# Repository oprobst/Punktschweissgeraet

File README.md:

# Punktschweissgeraet

Schaltpläne, Layouts und Software

See http://www.tief-dunkel-kalt.org/index.php/blog/42-diy-punktschweissgeraet for details (sorry, German only).

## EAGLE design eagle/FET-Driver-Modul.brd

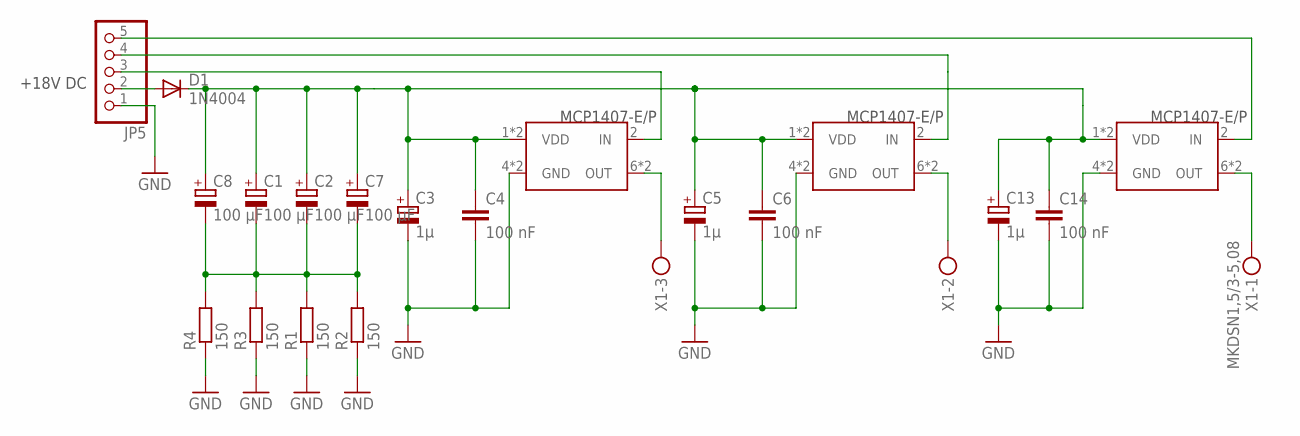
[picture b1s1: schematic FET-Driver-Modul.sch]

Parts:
C1, C2, C7, C8: 100 µF; E2,5-7
C3, C5, C13: 1µ; E5-8,5
C4, C6, C14: 100 nF; C0603
D1: 1N4004; DO41-10
JP5: PINHD-1X5; 1X05
R1, R2, R3, R4: 150; 0411/15
U$3, U$4, U$5: MCP1407MCP1407-DIL08; DIL-08
X1: MKDSN1,5/3-5,08

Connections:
GND: C3.-, C4.2, C5.-, C6.2, C13.-, C14.2, JP5.1, R1.1, R2.1, R3.1, R4.1, U$3.4 (GND), U$3.5 (GND), U$4.4 (GND), U$4.5 (GND), U$5.4 (GND), U$5.5 (GND)
unnamed: JP5.4, U$4.2 (IN)
unnamed: C1.+, C2.+, C3.+, C4.1, C5.+, C6.1, C7.+, C8.+, C13.+, C14.1, D1.C, U$3.1 (VDD), U$3.8 (VDD), U$4.1 (VDD), U$4.8 (VDD), U$5.1 (VDD), U$5.8 (VDD)
unnamed: JP5.5, U$5.2 (IN)
unnamed: C1.-, C2.-, C7.-, C8.-, R1.2, R2.2, R3.2, R4.2
unnamed: JP5.3, U$3.2 (IN)
unnamed: D1.A, JP5.2
unnamed: U$4.6 (OUT), U$4.7 (OUT), X1.2
unnamed: U$3.6 (OUT), U$3.7 (OUT), X1.3
unnamed: U$5.6 (OUT), U$5.7 (OUT), X1.1

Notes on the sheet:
+18V DC
MCP1407-E/P

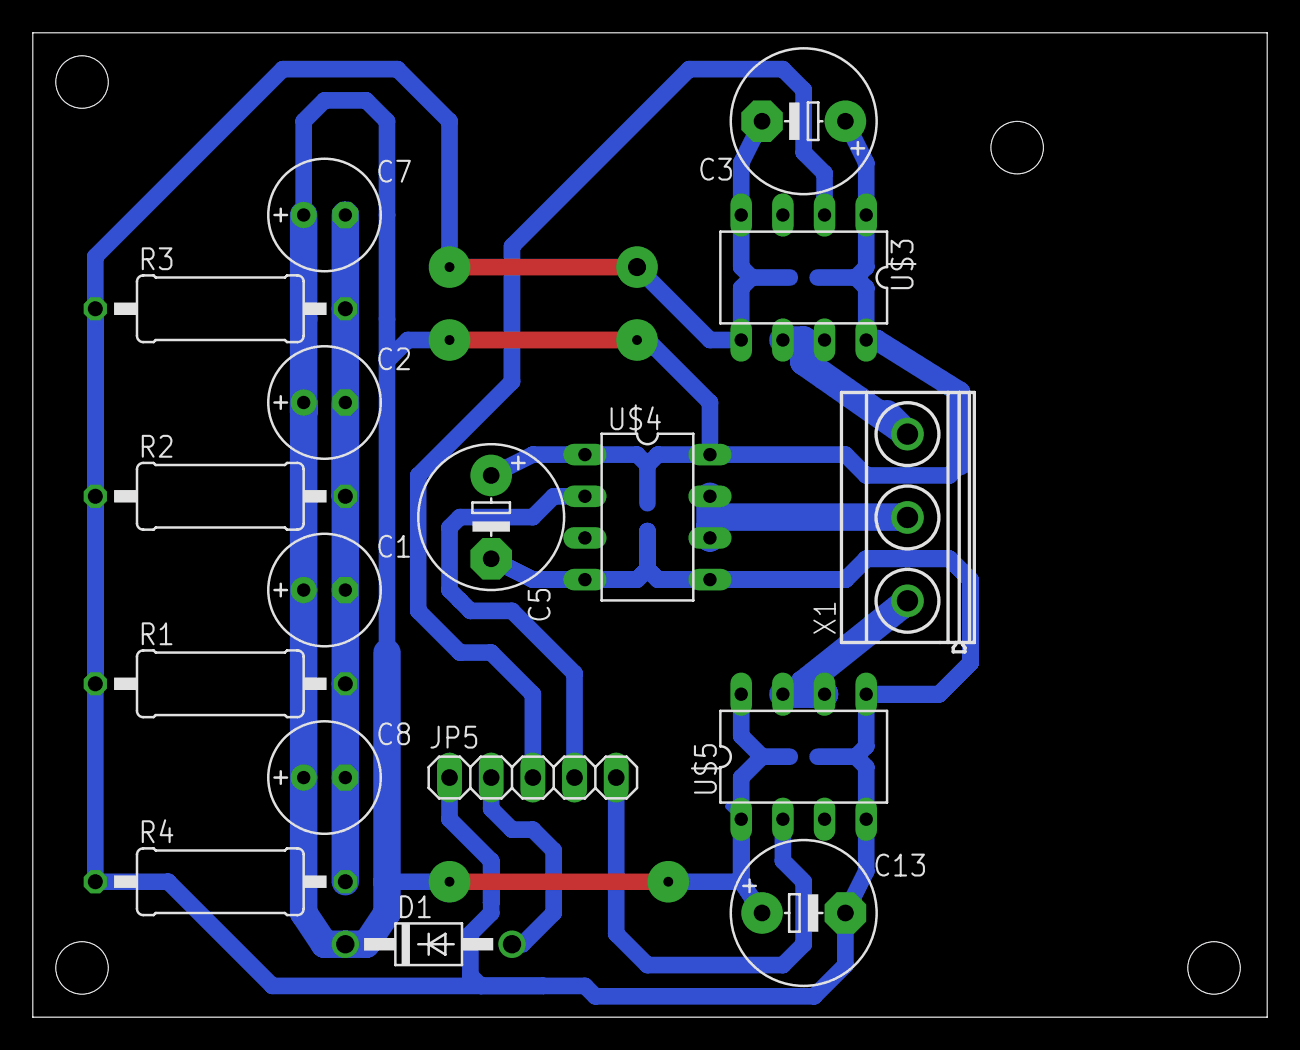
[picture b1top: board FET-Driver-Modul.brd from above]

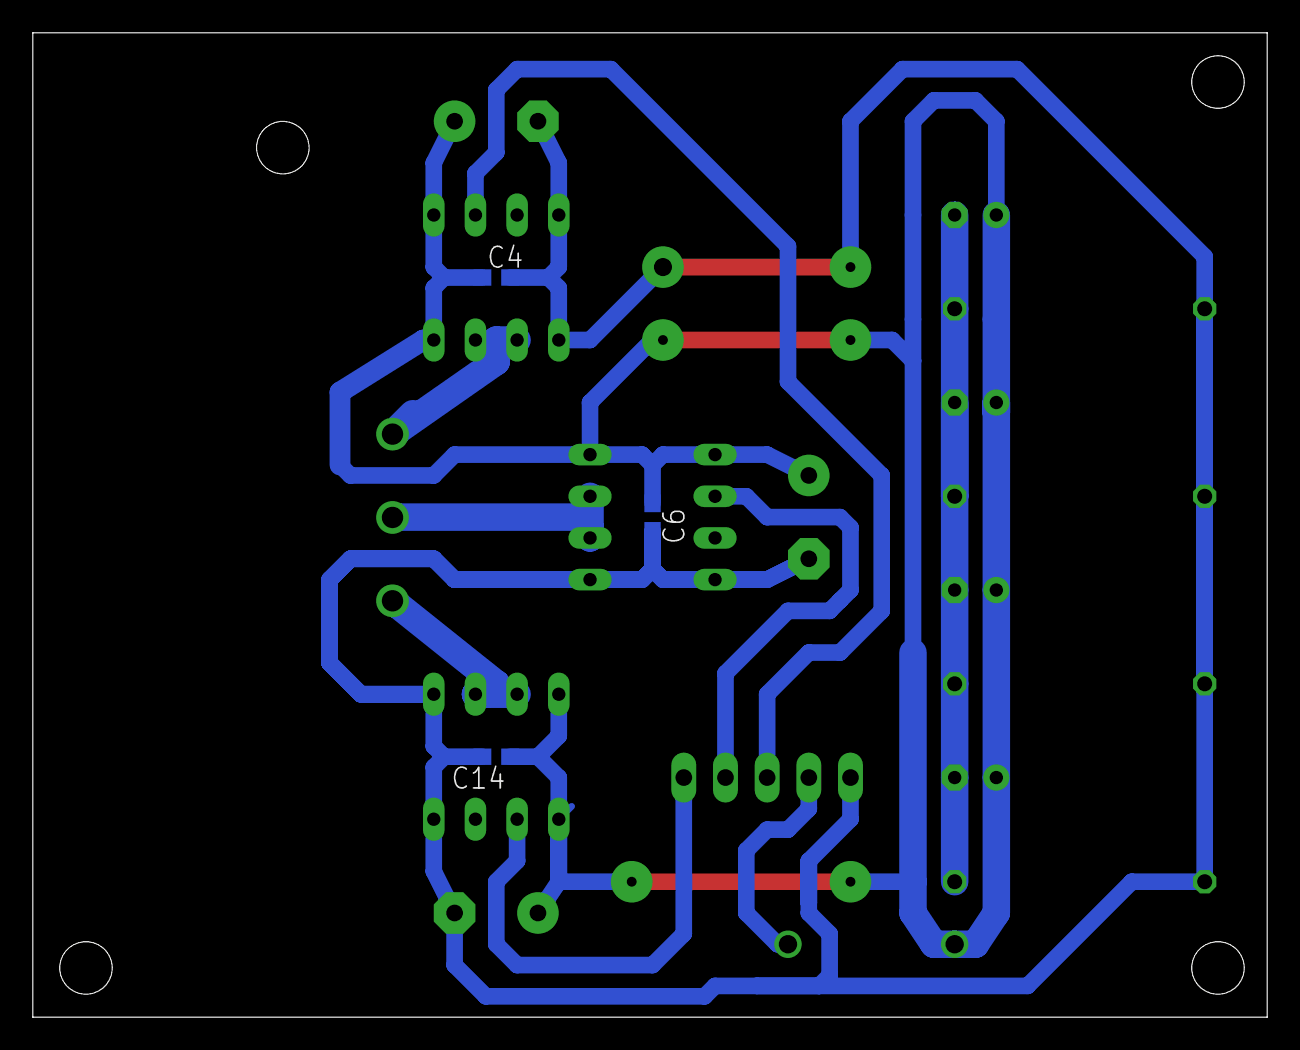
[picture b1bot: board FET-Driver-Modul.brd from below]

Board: 2 copper layers, 75.2 x 60.0 mm, 20 parts (3 on the bottom side), 10 nets.

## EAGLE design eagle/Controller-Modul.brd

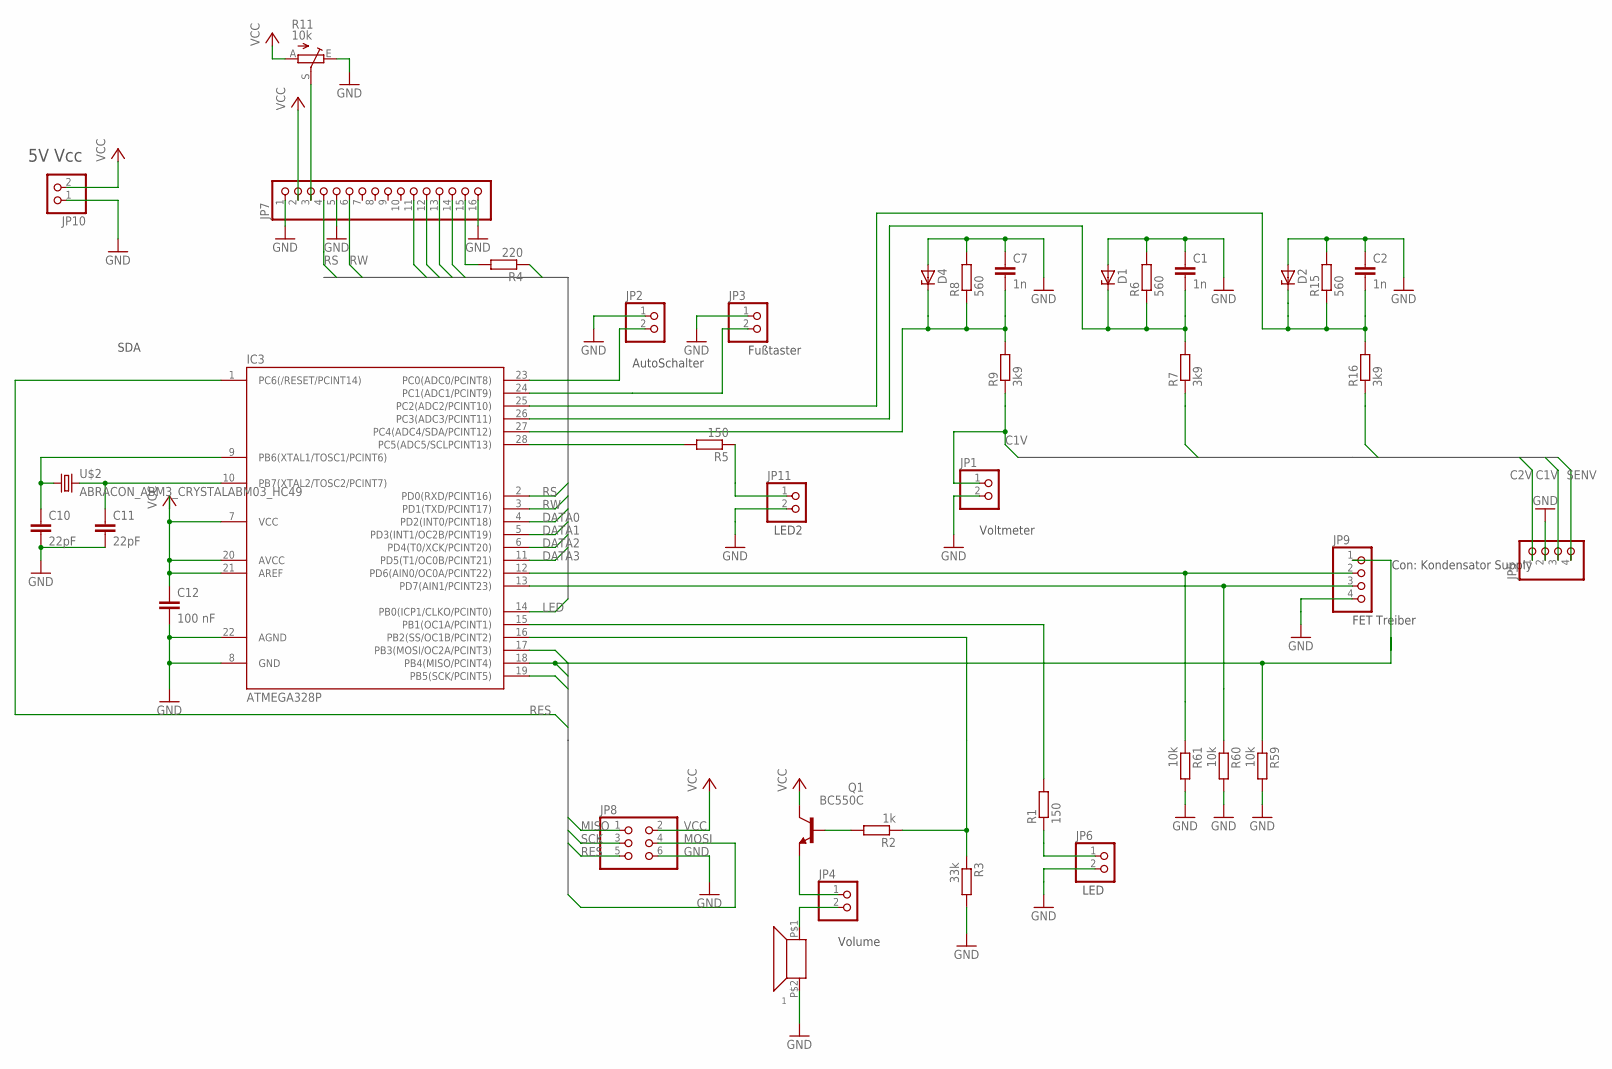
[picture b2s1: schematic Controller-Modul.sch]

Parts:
1: SUMMER4; PIEZO-INDIKATOR-KPMG
C1, C2, C7: 1n; C0603K
C10, C11: 22pF; C0603K
C12: 100 nF; C0603
D1, D2, D4: ZENER-DIODESOT23; SOT23
IC3: ATMEGA328P; DIL28-3
JP1, JP2, JP3, JP4, JP6, JP10, JP11: PINHD-1X2; 1X02
JP5, JP9: PINHD-1X4; 1X04
JP7: PINHD-1X16; 1X16
JP8: PINHD-2X3; 2X03
Q1: BC550C; TO92-EBC
R1, R5: 150; R1206
R2: 1k; R1206
R3: 33k; R1206
R4: 220; R1206
R6, R8, R15: 560; R1206
R7, R9, R16: 3k9; R1206
R11: 10k; PT-10
R59, R60, R61: 10k; R1206
U$2: ABRACON_ABM3_CRYSTALABM03_HC49; ABM03_HC49

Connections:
C1V: JP1.1, JP5.3, R9.1
C2V: JP5.1, R7.1
DATA0: IC3.4 (PD2(INT0/PCINT18)), JP7.11
DATA1: IC3.5 (PD3(INT1/OC2B/PCINT19)), JP7.12
DATA2: IC3.6 (PD4(T0/XCK/PCINT20)), JP7.13
DATA3: IC3.11 (PD5(T1/OC0B/PCINT21)), JP7.14
FET2: IC3.13 (PD7(AIN1/PCINT23)), JP9.3, R60.1
FET3: IC3.12 (PD6(AIN0/OC0A/PCINT22)), JP9.2, R61.1
GND: 1.P$2 (+), C1.1, C2.1, C7.1, C10.2, C11.2, C12.2, D1.1 (A), D2.1 (A), D4.1 (A), IC3.8 (GND), IC3.22 (AGND), JP1.2, JP2.1, JP3.1, JP5.2, JP6.2, JP7.1, JP7.5, JP7.16, JP8.6, JP9.4, JP10.1, JP11.2, R3.2, R6.2, R8.2, R11.E, R15.2, R59.2, R60.2, R61.2
LED: IC3.14 (PB0(ICP1/CLKO/PCINT0)), R4.1
MISO: IC3.18 (PB4(MISO/PCINT4)), JP8.1, JP9.1, R59.1
MOSI: IC3.17 (PB3(MOSI/OC2A/PCINT3)), JP8.4
unnamed: JP11.1, R5.1
unnamed: IC3.28 (PC5(ADC5/SCLPCINT13)), R5.2
unnamed: Q1.B, R2.2
unnamed: C7.2, D4.3 (C), IC3.27 (PC4(ADC4/SDA/PCINT12)), R8.1, R9.2
unnamed: JP6.1, R1.1
unnamed: C1.2, D1.3 (C), IC3.26 (PC3(ADC3/PCINT11)), R6.1, R7.2
unnamed: IC3.16 (PB2(SS/OC1B/PCINT2)), R2.1, R3.1
unnamed: IC3.23 (PC0(ADC0/PCINT8)), JP2.2
unnamed: JP4.1, Q1.E
unnamed: IC3.24 (PC1(ADC1/PCINT9)), JP3.2
unnamed: 1.P$1 (-), JP4.2
unnamed: C2.2, D2.3 (C), IC3.25 (PC2(ADC2/PCINT10)), R15.1, R16.2
unnamed: IC3.15 (PB1(OC1A/PCINT1)), R1.2
unnamed: C11.1, IC3.10 (PB7(XTAL2/TOSC2/PCINT7)), U$2.2
unnamed: C10.1, IC3.9 (PB6(XTAL1/TOSC1/PCINT6)), U$2.1
unnamed: JP7.3, R11.S
unnamed: JP7.15, R4.2
RES: IC3.1 (PC6(/RESET/PCINT14)), JP8.5
RS: IC3.2 (PD0(RXD/PCINT16)), JP7.4
RW: IC3.3 (PD1(TXD/PCINT17)), JP7.6
SCK: IC3.19 (PB5(SCK/PCINT5)), JP8.3
SENV: JP5.4, R16.1
VCC: C12.1, IC3.7 (VCC), IC3.20 (AVCC), IC3.21 (AREF), JP7.2, JP8.2, JP10.2, Q1.C, R11.A

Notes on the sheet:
SDA
5V Vcc
LED
Volume
Con: Kondensator Supply
Voltmeter
Fußtaster
AutoSchalter
FET Treiber
LED2

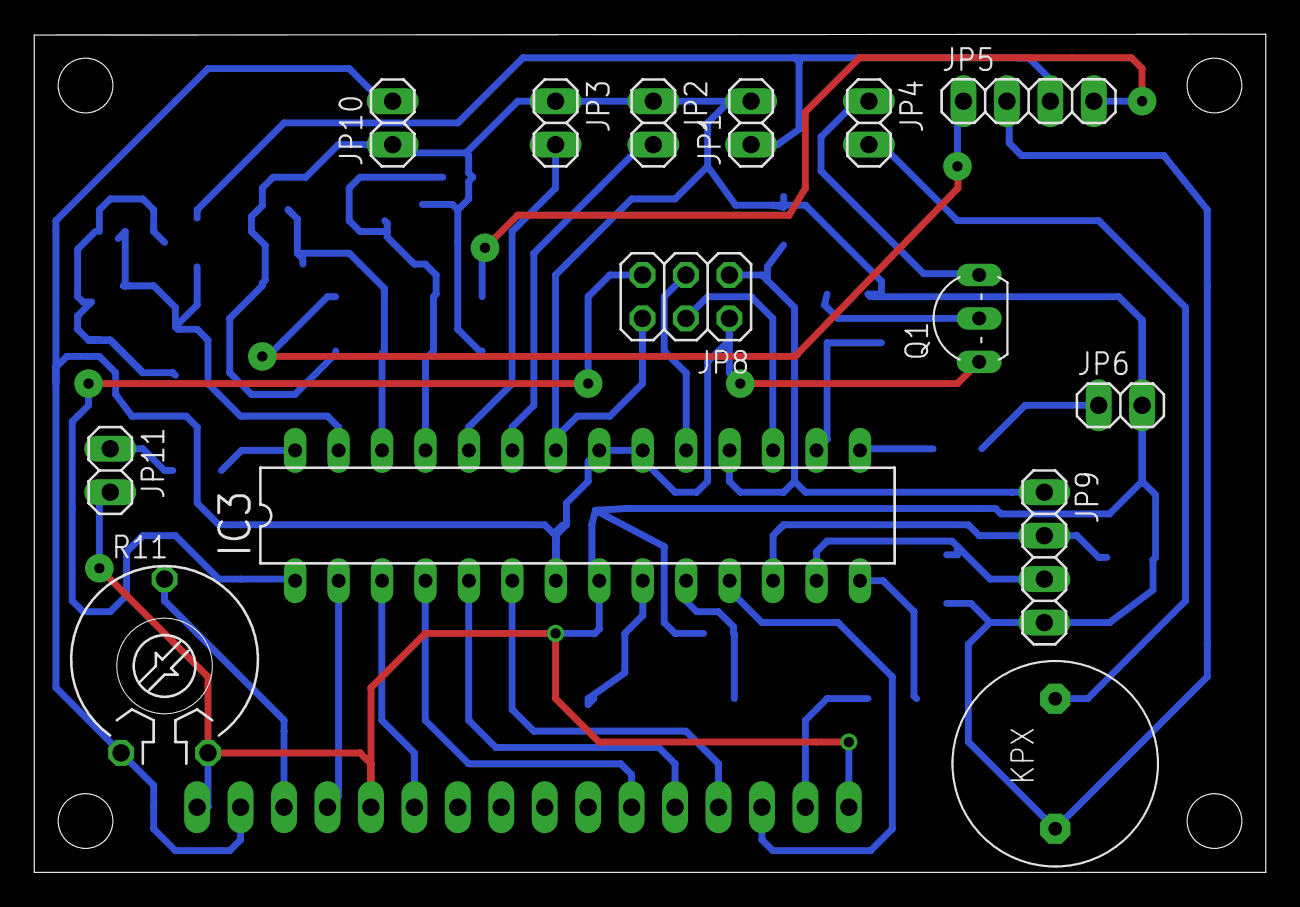
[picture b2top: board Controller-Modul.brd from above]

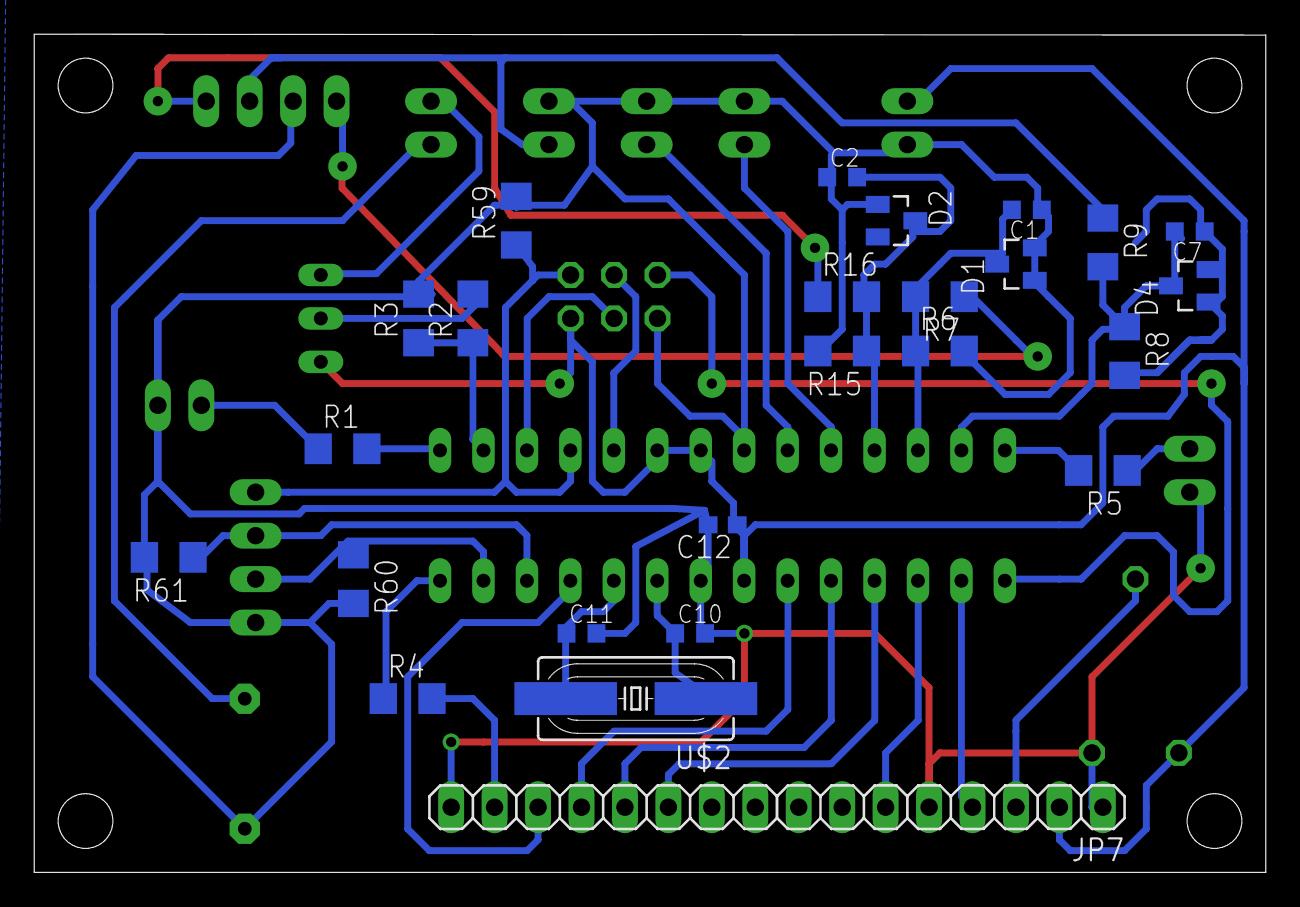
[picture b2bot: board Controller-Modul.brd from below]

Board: 2 copper layers, 72.0 x 49.0 mm, 39 parts (25 on the bottom side), 35 nets.

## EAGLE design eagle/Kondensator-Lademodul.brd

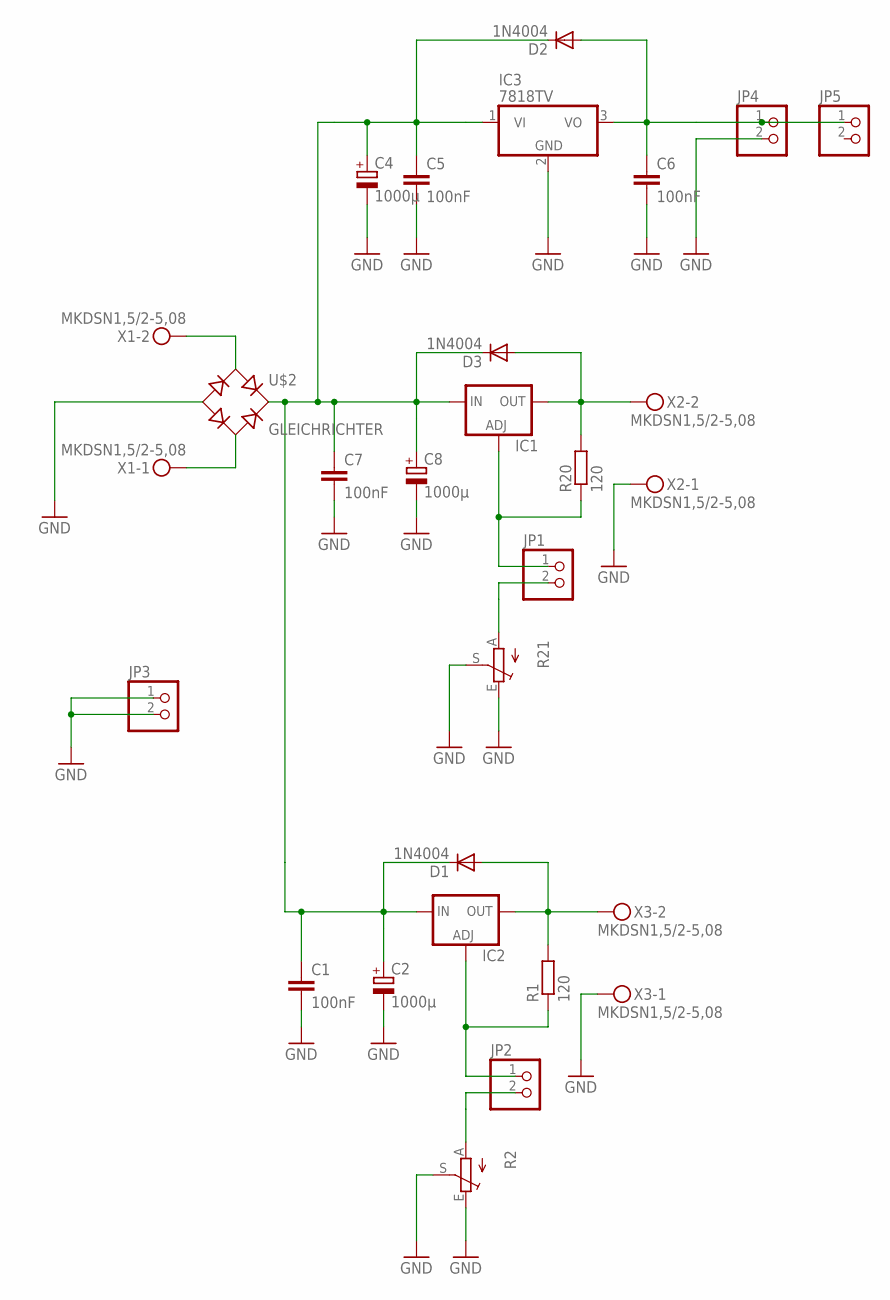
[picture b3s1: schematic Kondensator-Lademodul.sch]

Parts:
C1, C5, C6, C7: 100nF; C0805
C2, C4, C8: 1000µ; E5-13
D1, D2, D3: 1N4004; DO41-10
IC1, IC2: LM317TS; 317TS
IC3: 7818TV; TO220V
JP1, JP2, JP3, JP4, JP5: PINHD-1X2; 1X02
R1, R20: 120; R1206
R2, R21: TRIM_EU-PT10; PT-10
U$2: GLEICHRICHTER; KBPC1
X1, X2, X3: MKDSN1,5/2-5,08

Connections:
GND: C1.2, C2.-, C4.-, C5.2, C6.2, C7.2, C8.-, IC3.2 (GND), JP3.1, JP3.2, JP4.2, JP5.2, R2.E, R2.S, R21.E, R21.S, U$2.-, X2.1, X3.1
unnamed: C6.1, D2.A, IC3.3 (VO), JP4.1, JP5.1
unnamed: D1.A, IC2.2 (OUT), R1.2, X3.2
unnamed: IC2.1 (ADJ), JP2.1, R1.1
unnamed: JP2.2, R2.A
unnamed: C1.1, C2.+, C4.+, C5.1, C7.1, C8.+, D1.C, D2.C, D3.C, IC1.3 (IN), IC2.3 (IN), IC3.1 (VI), U$2.+
unnamed: U$2.AC1, X1.2
unnamed: U$2.AC2, X1.1
unnamed: D3.A, IC1.2 (OUT), R20.2, X2.2
unnamed: JP1.2, R21.A
unnamed: IC1.1 (ADJ), JP1.1, R20.1

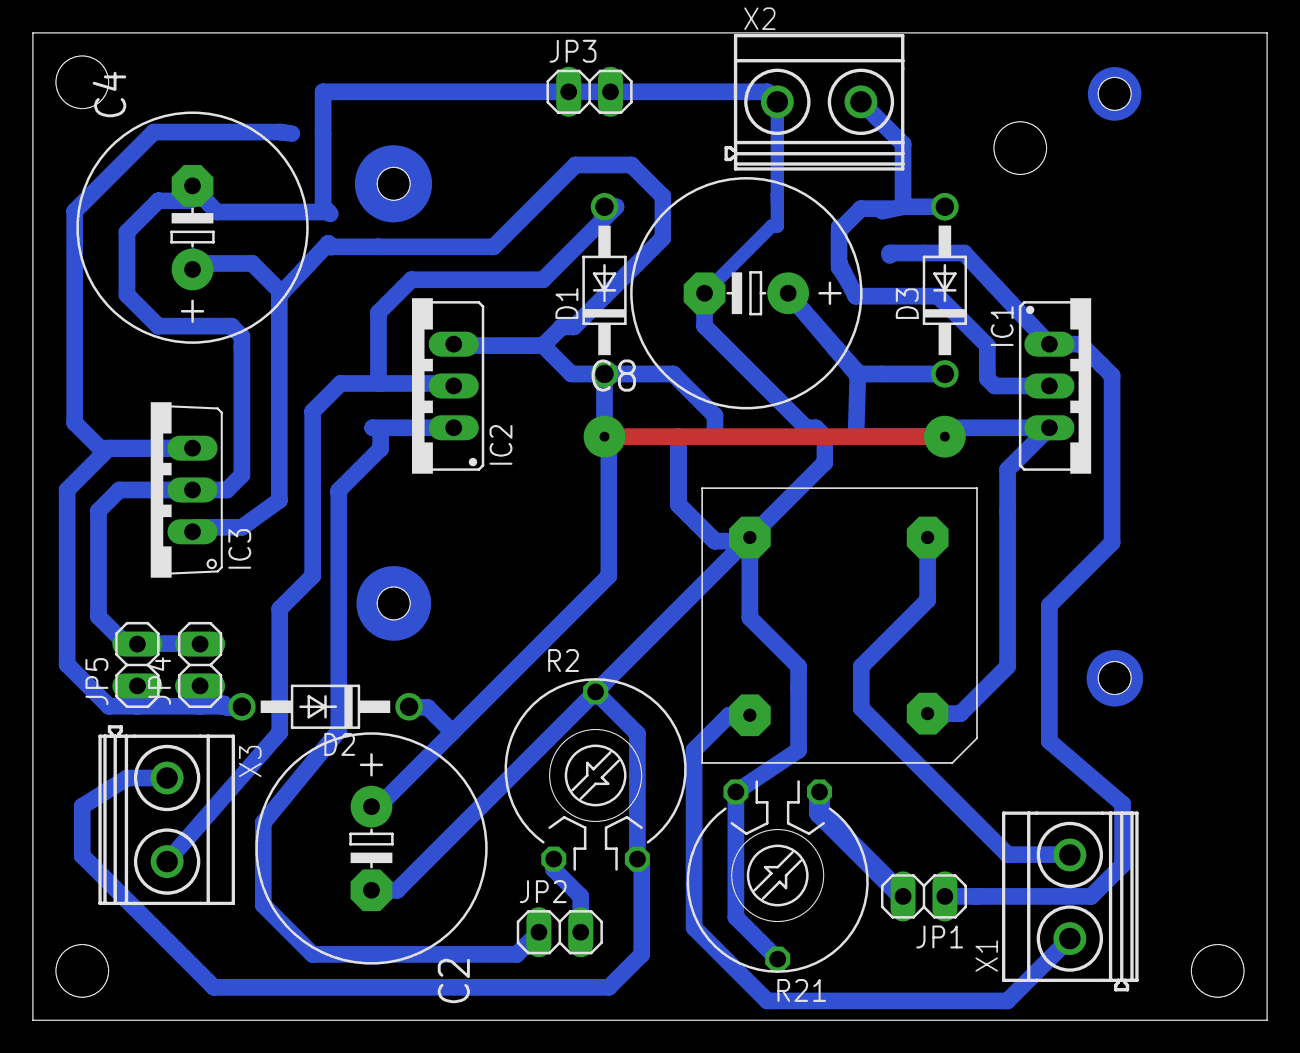
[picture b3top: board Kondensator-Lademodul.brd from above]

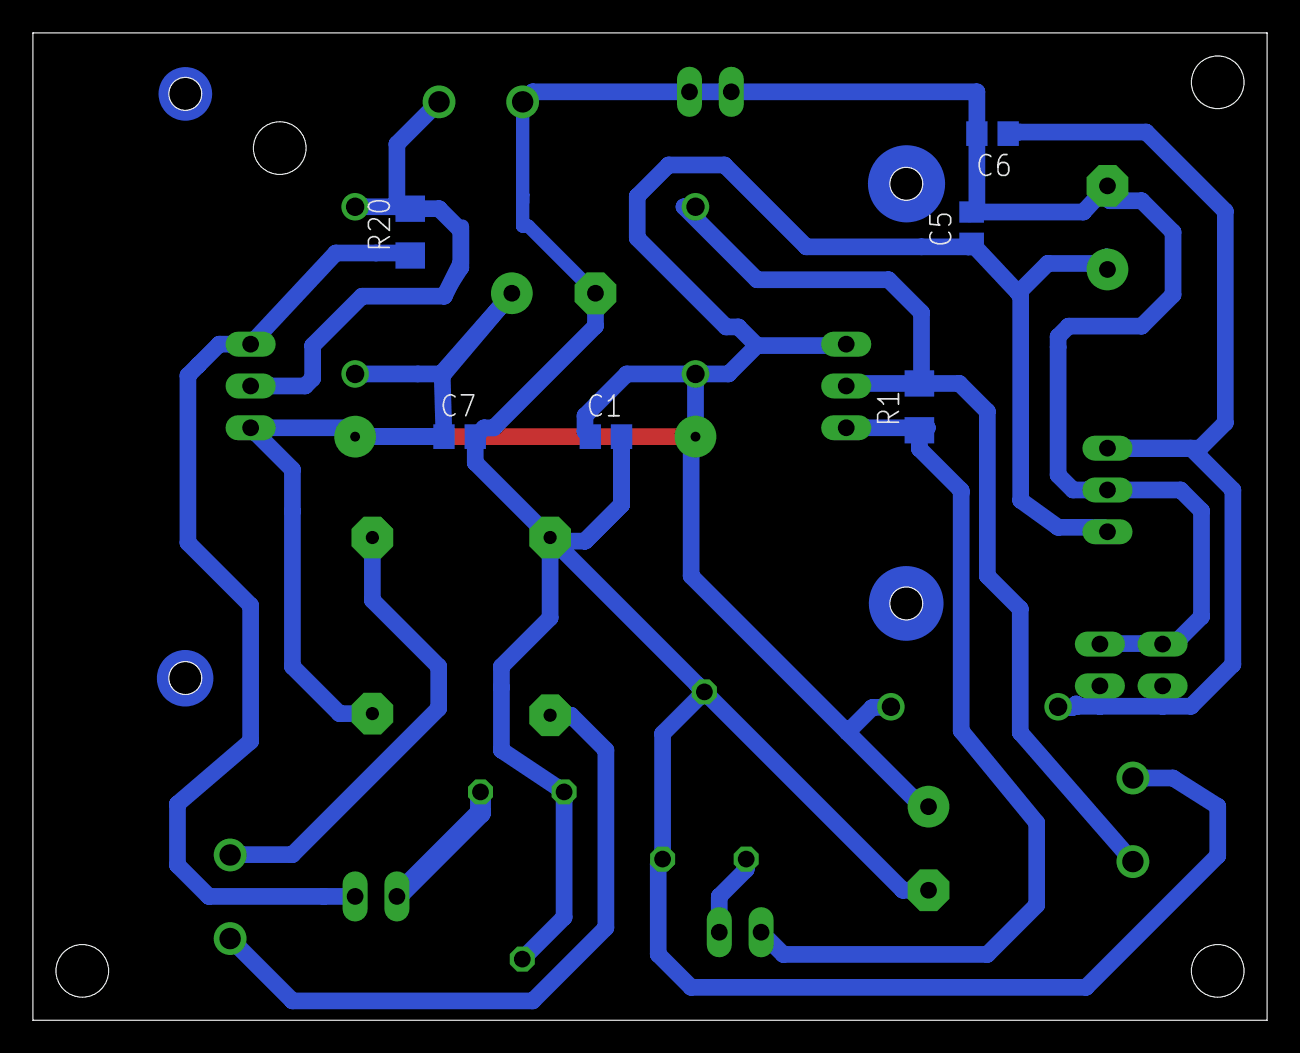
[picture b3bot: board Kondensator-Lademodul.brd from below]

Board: 2 copper layers, 75.0 x 60.0 mm, 26 parts (6 on the bottom side), 11 nets.

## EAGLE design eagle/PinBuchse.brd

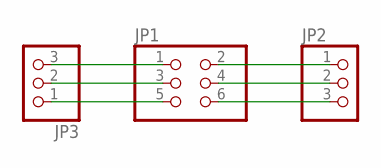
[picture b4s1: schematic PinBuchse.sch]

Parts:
JP1: PINHD-2X3; 2X03
JP2, JP3: PINHD-1X3; 1X03

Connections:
unnamed: JP1.1, JP3.3
unnamed: JP1.3, JP3.2
unnamed: JP1.5, JP3.1
unnamed: JP1.2, JP2.1
unnamed: JP1.4, JP2.2
unnamed: JP1.6, JP2.3

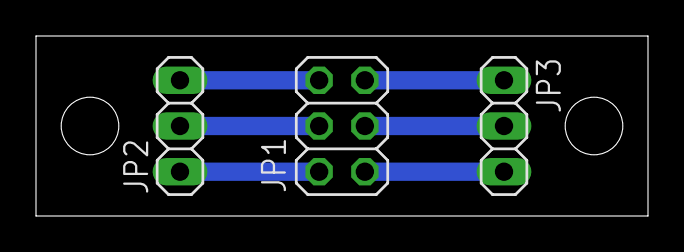
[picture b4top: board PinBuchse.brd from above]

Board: 2 copper layers, 34.0 x 10.0 mm, 3 parts (0 on the bottom side), 6 nets.

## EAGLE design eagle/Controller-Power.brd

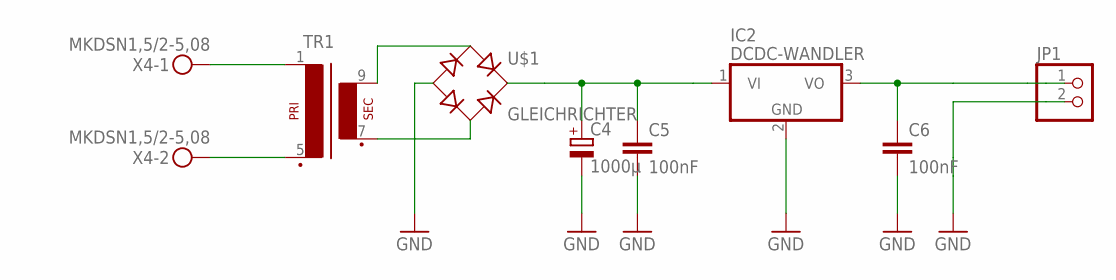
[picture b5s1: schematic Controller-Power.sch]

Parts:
C4: 1000µ; E3,5-8
C5, C6: 100nF; C0805
IC2: DCDC-WANDLER; TRACOPOWER-DCDCWANDER-TSR1
JP1: PINHD-1X2; 1X02
TR1: EI38-1
U$1: GLEICHRICHTER; KBPC1
X4: MKDSN1,5/2-5,08

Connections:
GND: C4.-, C5.2, C6.2, IC2.2 (GND), JP1.2, U$1.-
unnamed: C4.+, C5.1, IC2.1 (VI), U$1.+
unnamed: TR1.1, X4.1
unnamed: TR1.5 (P2), X4.2
unnamed: TR1.7 (S3), U$1.AC2
unnamed: TR1.9 (S4), U$1.AC1
unnamed: C6.1, IC2.3 (VO), JP1.1

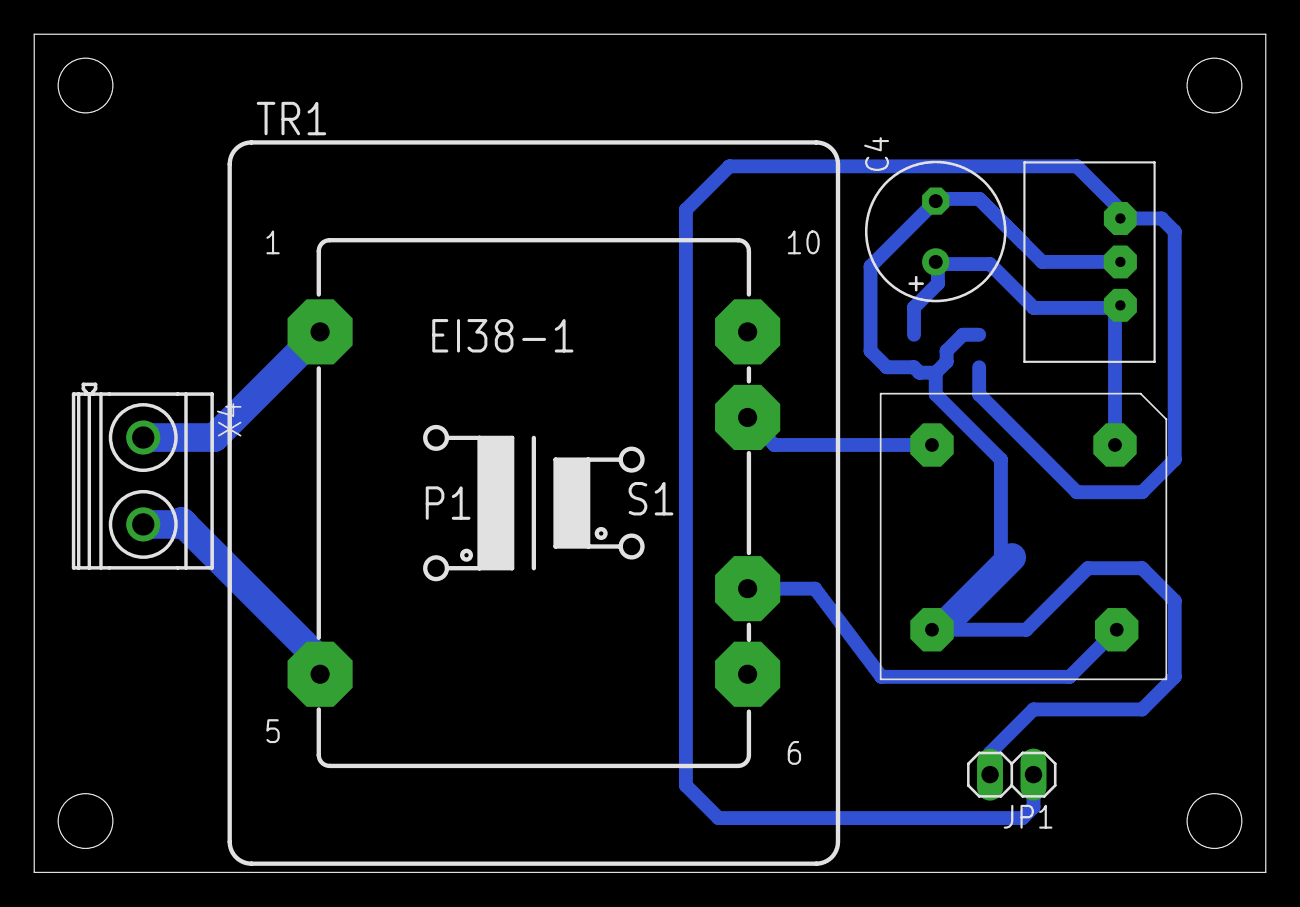
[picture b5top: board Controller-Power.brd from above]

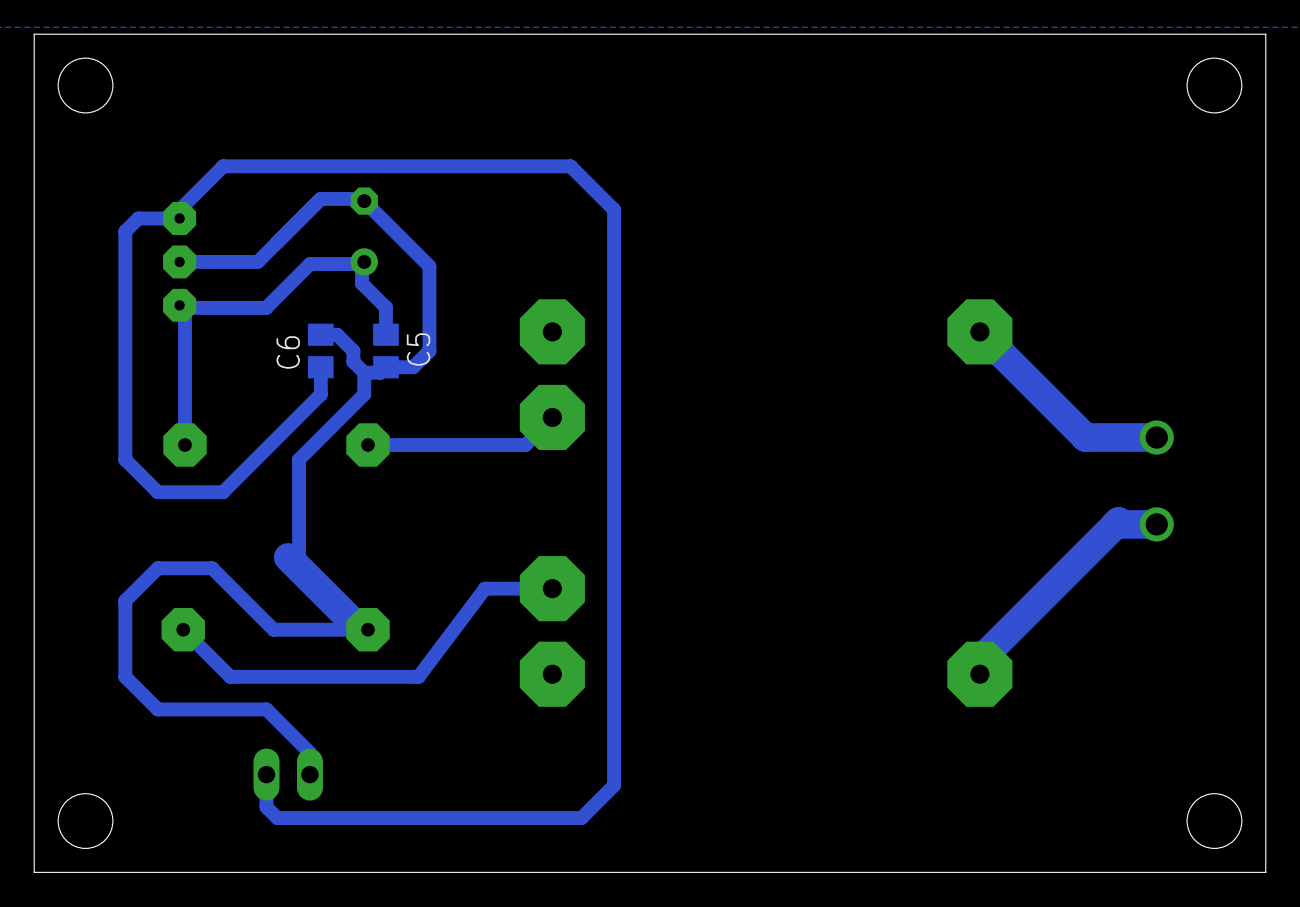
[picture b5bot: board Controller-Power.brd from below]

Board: 2 copper layers, 72.0 x 49.0 mm, 8 parts (2 on the bottom side), 7 nets.

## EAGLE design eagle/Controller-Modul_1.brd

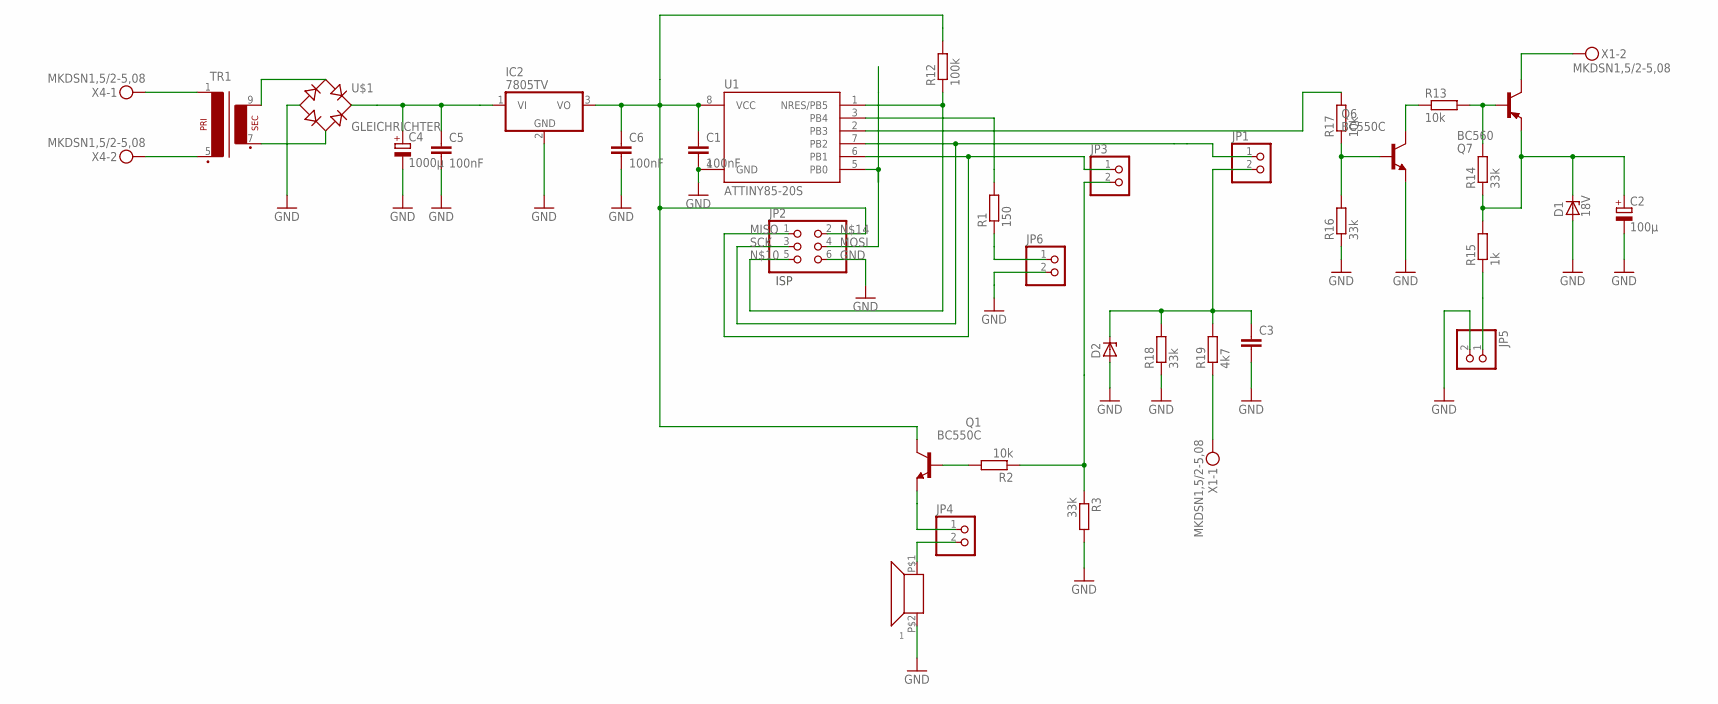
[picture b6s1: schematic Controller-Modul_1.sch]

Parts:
1: SUMMER4; PIEZO-INDIKATOR-KPMG
C1, C5, C6: 100nF; C0805
C2: 100µ; E2,5-7
C3: C-EUC0603K; C0603K
C4: 1000µ; E3,5-8
D1: 18V; SOD80C
D2: ZENER-DIODESOT23; SOT23
IC2: 7805TV; TO220V
JP1, JP3, JP4, JP5, JP6: PINHD-1X2; 1X02
JP2: PINHD-2X3; 2X03
Q1, Q6: BC550C; TO92-EBC
Q7: BC560; TO92-EBC
R1: 150; R1206
R2, R13, R17: 10k; R1206
R3, R14, R16, R18: 33k; R1206
R12: 100k; R1206
R15: 1k; R1206
R19: 4k7; R1206
TR1: EI38-1
U1: ATTINY85-20S; SOIC8_EIAJ_208MIL
U$1: GLEICHRICHTER; KBPC1
X1, X4: MKDSN1,5/2-5,08

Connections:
GND: 1.P$2 (+), C1.2, C2.-, C3.2, C4.-, C5.2, C6.2, D1.A, D2.1 (A), IC2.2 (GND), JP2.6, JP5.2, JP6.2, Q6.E, R3.2, R16.1, R18.1, U1.4 (GND), U$1.-
MISO: JP2.1, JP3.1, U1.6 (PB1)
MOSI: JP2.4, U1.5 (PB0)
unnamed: Q7.B, R13.2, R14.2
unnamed: C3.1, D2.3 (C), JP1.2, R18.2, R19.2
unnamed: Q6.B, R16.2, R17.1
unnamed: Q1.B, R2.2
unnamed: Q6.C, R13.1
unnamed: JP6.1, R1.1
unnamed: R19.1, X1.1
unnamed: C2.+, D1.C, Q7.E, R14.1, R15.2
unnamed: JP3.2, R2.1, R3.1
unnamed: JP2.5, R12.1, U1.1 (NRES/PB5)
unnamed: JP4.1, Q1.E
unnamed: R1.2, U1.3 (PB4)
unnamed: 1.P$1 (-), JP4.2
unnamed: C1.1, C6.1, IC2.3 (VO), JP2.2, Q1.C, R12.2, U1.8 (VCC)
unnamed: JP5.1, R15.1
unnamed: C4.+, C5.1, IC2.1 (VI), U$1.+
unnamed: Q7.C, X1.2
unnamed: TR1.1, X4.1
unnamed: TR1.5 (P2), X4.2
unnamed: TR1.7 (S3), U$1.AC2
unnamed: TR1.9 (S4), U$1.AC1
unnamed: R17.2, U1.2 (PB3)
SCK: JP1.1, JP2.3, U1.7 (PB2)

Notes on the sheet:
ISP

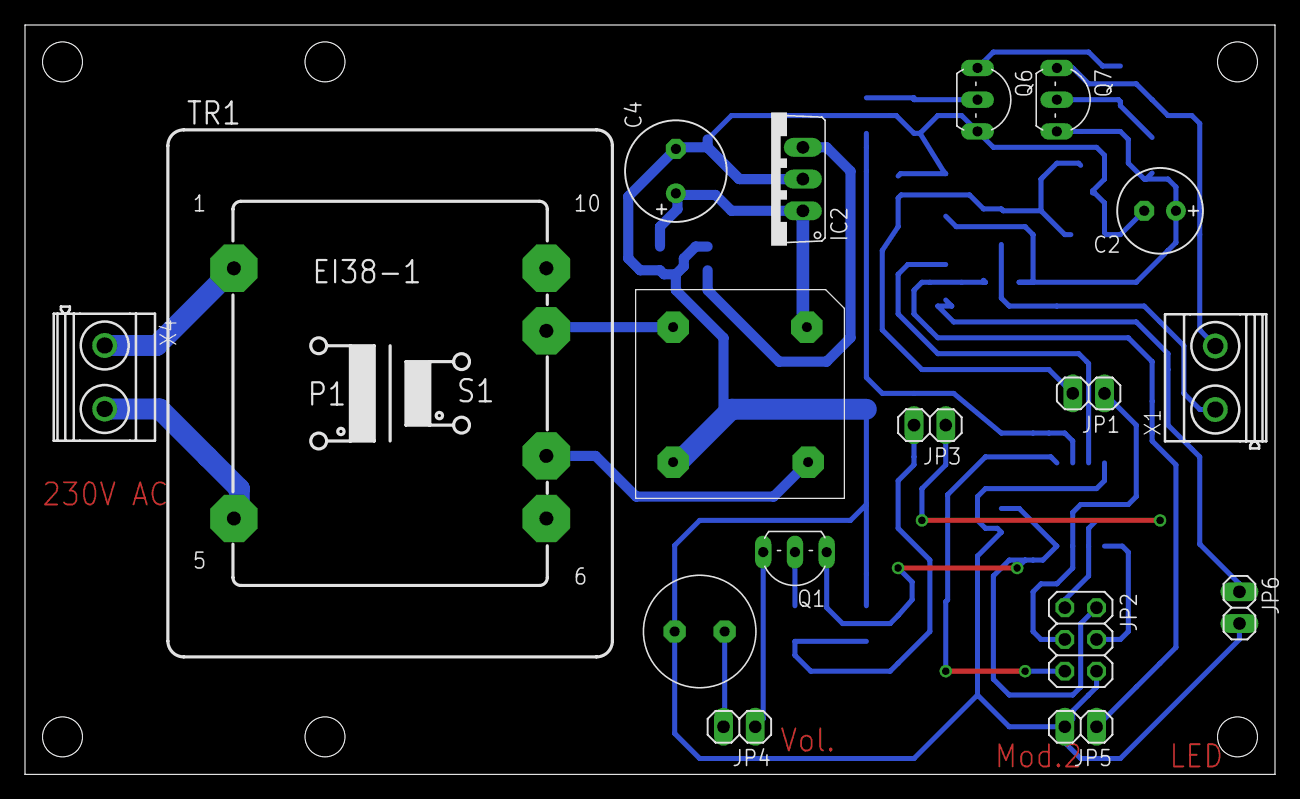
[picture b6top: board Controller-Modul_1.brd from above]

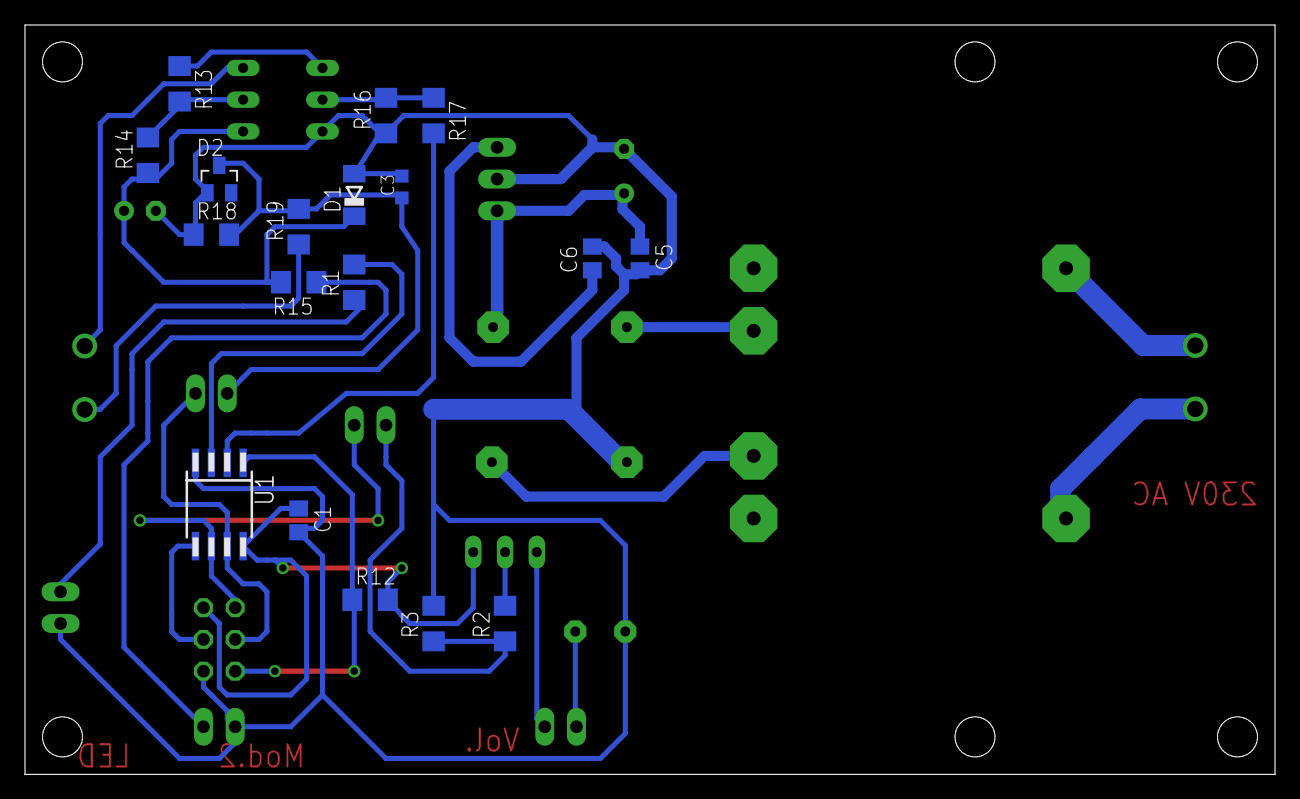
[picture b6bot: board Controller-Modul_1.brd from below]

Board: 2 copper layers, 100.0 x 60.0 mm, 35 parts (18 on the bottom side), 26 nets.

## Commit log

2016-02-28 Added files
2016-03-01 Added fet driver
2016-03-01 pcb design
2016-03-02 Lots of schema and board changes
2016-03-03 Adjusted drill positions, little size corrections, new pin header
2016-03-14 Fixed setup of capacitors (bigger and not in conflict)
2016-03-20 Var. Changes. Layout and new diode for 7818
2016-03-22 Added first version of source code files
2016-03-22 Lots of code mainly for lcd
2016-04-02 Updated wrong resistor value
2016-05-04 Added 'Gesamtschaltplan'
2016-05-04 added debug output to lcd, little fix for disabling execution on low voltage
2016-05-04 Function to measure voltage
2016-05-06 Reworked the eeprom safe and load mechanism Added functionality for calibrating caps
2016-05-07 Mainly worked on calibration. Some ui stuff as well. Removed 22k Resistor.
2016-05-07 Removed 22k Resistor
2016-05-08 Corrected wrong direction of zener diodes
2016-05-08 A lot of timer stuff for calibration added
2016-05-08 Added "improvement" chapter
2016-05-09 trying to measure amperes during execution
2016-05-13 Added forgotten Pull-Down resistors. Lots of new code for executing mosfets
2016-06-26 Minor documentation changes, reduced size of vsens Resistor to detect contact
2016-06-26 Formatting issues displaying ampere and ohm
2016-06-26 Reduced contact voltage boundary
2016-06-27 fix: Ampere now measured, read/write executions saved correctly
2016-06-27 additional diode at Mosfet driver
2016-06-30 added diode to driver power supply
2016-06-30 Added option to measure discharge curve
2016-06-30 Added missing GND connector for mosfet driver
2016-06-30 Enhanced calculation of aprox. current
